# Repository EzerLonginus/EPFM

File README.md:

# EPFM
Building out the projects from Craig Anderton's Book Electronic Projects for Musicians.  

<p>This book was a primary inspiration for me when I was growing up, and I've always wanted to actually complete a good amount of these projects.  The parts listed in the projects were always obsolete or difficult to source.  Having a little more experience than when I was a kid, I took to time to revisit some of these projects.  Not sure I'll post all the projects, since some aren't really projects ("PROJECT 19: Using a Volt Ohm-Millameter"), but maybe I'll try post something in the spirit of those projects.</p>

## OBJECTIVES
- Modify existing schematics with parts that are currently in stock and with similar electrical properties<
- Try to design the PCBs for through hole components to make it easier for more people to create the boards
- Design the PCBs to be friendly with desktop PCB milling machines should one choose to go that route.
    - I tried to keep most of the traces on the bottom side of the board
    - Where top side traces where necessary I kept those straight with large vias so people could just use a jumper wire
- Design the boards and face plate to fit within the Eurorack standard
- Document additional modifications and findings

## PROJECTS (so far)
- PREAMP
- METRONOME
- PASSIVE TONE CONTROL
- HEADPHONE AMP
- MINI AMP
- ULTRA FUZZ

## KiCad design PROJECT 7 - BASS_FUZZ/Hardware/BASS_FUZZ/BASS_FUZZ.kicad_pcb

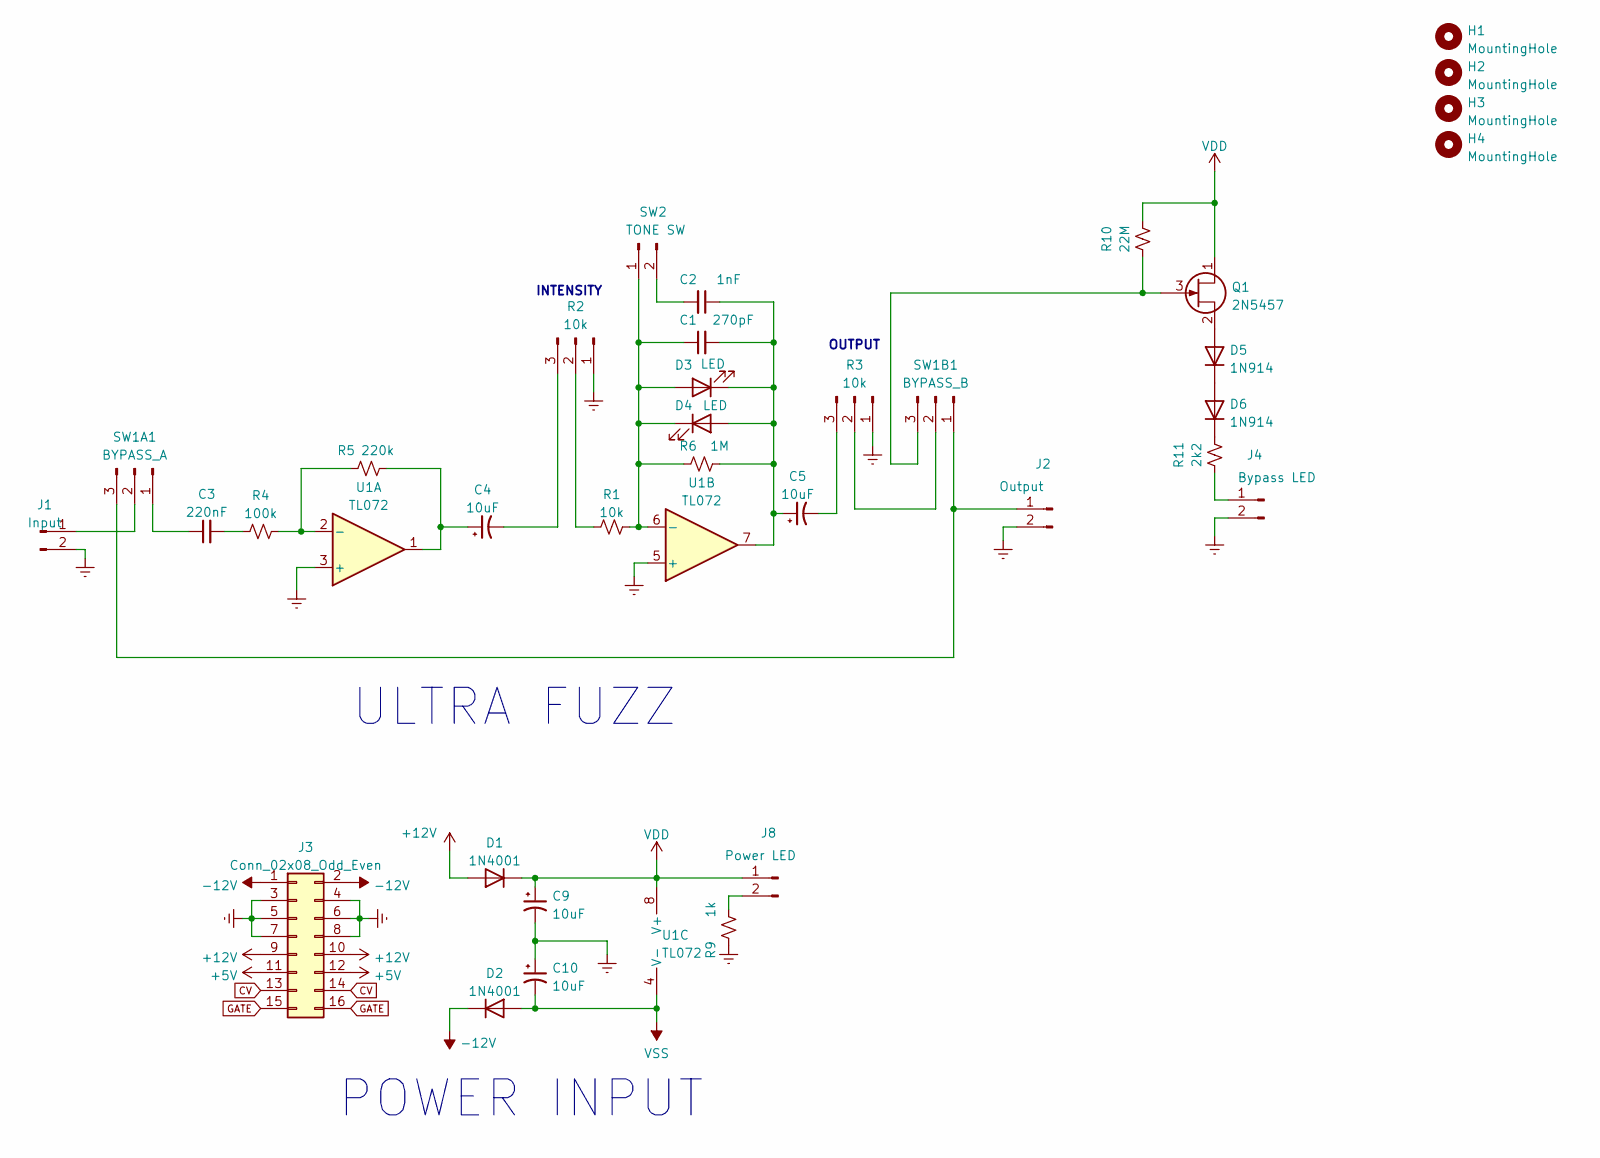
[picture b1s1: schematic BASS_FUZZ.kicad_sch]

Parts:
C1: 270pF; C_Disc_D5.0mm_W2.5mm_P5.00mm
C2: 1nF; C_Disc_D5.0mm_W2.5mm_P5.00mm
C3: 220nF; C_Disc_D5.0mm_W2.5mm_P5.00mm
C4, C5: 10uF; CP_Radial_D8.0mm_P3.80mm
C9, C10: 10uF; CP_Radial_D10.0mm_P3.80mm
D1, D2: 1N4001; D_DO-41_SOD81_P10.16mm_Horizontal
D3, D4: LED; LED_D5.0mm
D5, D6: 1N914; D_DO-35_SOD27_P7.62mm_Horizontal
H1, H2, H3, H4: MountingHole; MountingHole_3.2mm_M3_DIN965_Pad
J1: Input; Molex_SL_171971-0002_1x02_P2.54mm_Vertical
J2: Output; Molex_SL_171971-0002_1x02_P2.54mm_Vertical
J3: Conn_02x08_Odd_Even; IDC-Header_2x08_P2.54mm_Vertical
J4: Bypass LED; Molex_SL_171971-0002_1x02_P2.54mm_Vertical
J8: Power LED; Molex_SL_171971-0002_1x02_P2.54mm_Vertical
Q1: 2N5457; TO-92L_Inline_Wide
R1: 10k; R_Axial_DIN0207_L6.3mm_D2.5mm_P7.62mm_Horizontal
R2, R3: 10k; Molex_SL_171971-0003_1x03_P2.54mm_Vertical
R4: 100k; R_Axial_DIN0207_L6.3mm_D2.5mm_P7.62mm_Horizontal
R5: 220k; R_Axial_DIN0207_L6.3mm_D2.5mm_P7.62mm_Horizontal
R6: 1M; R_Axial_DIN0207_L6.3mm_D2.5mm_P7.62mm_Horizontal
R9: 1k; R_Axial_DIN0207_L6.3mm_D2.5mm_P7.62mm_Horizontal
R10: 22M; R_Axial_DIN0207_L6.3mm_D2.5mm_P7.62mm_Horizontal
R11: 2k2; R_Axial_DIN0207_L6.3mm_D2.5mm_P7.62mm_Horizontal
SW1A1: BYPASS_A; Molex_SL_171971-0003_1x03_P2.54mm_Vertical
SW1B1: BYPASS_B; Molex_SL_171971-0003_1x03_P2.54mm_Vertical
SW2: TONE SW; Molex_SL_171971-0002_1x02_P2.54mm_Vertical
U1: TL072; DIP-8_W7.62mm_Socket_LongPads

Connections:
+5V: J3.11, J3.12
+12V: D1.2 (A), J3.9, J3.10
-12V: D2.1 (K), J3.1, J3.2
CV: J3.13, J3.14
Earth: C9.2, C10.1, J1.2, J2.2, J3.3, J3.4, J3.5, J3.6, J3.7, J3.8, J4.2, R2.1, R3.1, R9.1, U1.3 (+), U1.5 (+)
GATE: J3.15, J3.16
unnamed: C3.1, SW1A1.1
unnamed: C3.2, R4.1
unnamed: D5.1 (K), D6.2 (A)
unnamed: D5.2 (A), Q1.2 (S)
unnamed: D6.1 (K), R11.2
unnamed: J1.1, SW1A1.2
unnamed: J2.1, SW1A1.3, SW1B1.1
unnamed: J4.1, R11.1
unnamed: J8.2, R9.2
unnamed: Q1.3 (G), R10.1, SW1B1.3
unnamed: R1.1, R2.2
unnamed: C4.2, R2.3
unnamed: C5.2, R3.3
unnamed: R4.2, R5.1, U1.2 (-)
unnamed: C4.1, R5.2, U1.1
unnamed: C1.2, C2.1, C5.1, D3.1 (K), D4.2 (A), R6.2, U1.7
unnamed: R3.2, SW1B1.2
unnamed: C2.2, SW2.2
unnamed: C1.1, D3.2 (A), D4.1 (K), R1.2, R6.1, SW2.1, U1.6 (-)
VDD: C9.1, D1.1 (K), J8.1, Q1.1 (D), R10.2, U1.8 (V+)
VSS: C10.2, D2.2 (A), U1.4 (V-)

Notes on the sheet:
POWER INPUT
OUTPUT
INTENSITY
ULTRA FUZZ

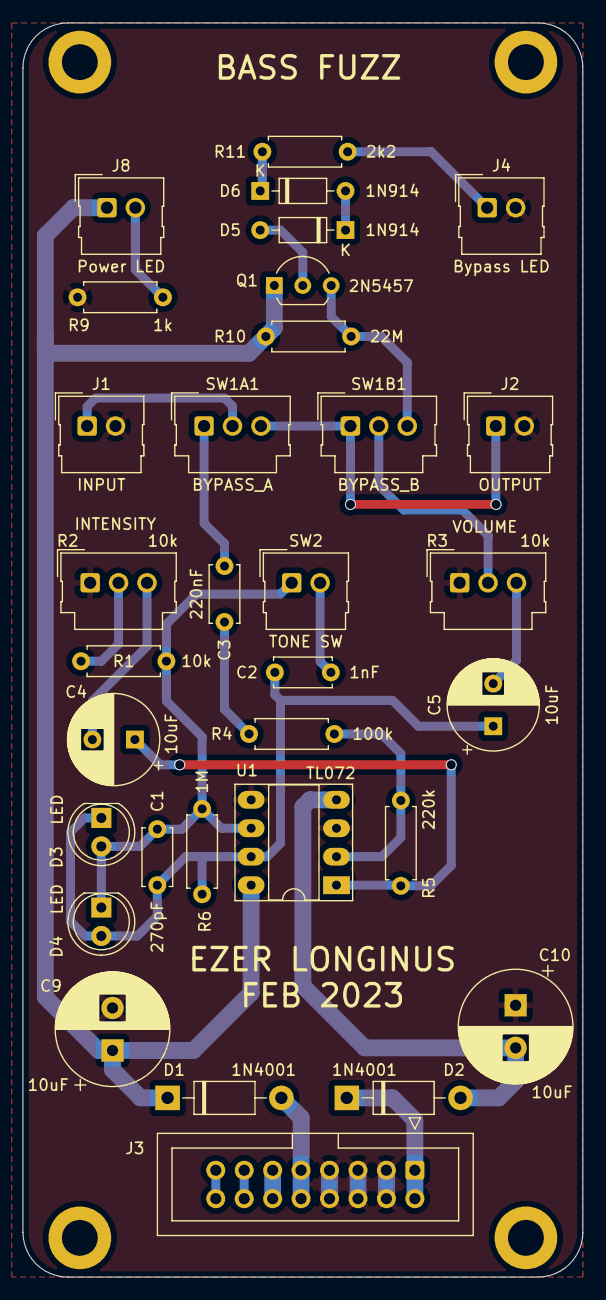
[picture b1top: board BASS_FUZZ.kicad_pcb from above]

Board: 2 copper layers, 50.0 x 112.0 mm, 36 parts (0 on the bottom side), 27 nets.

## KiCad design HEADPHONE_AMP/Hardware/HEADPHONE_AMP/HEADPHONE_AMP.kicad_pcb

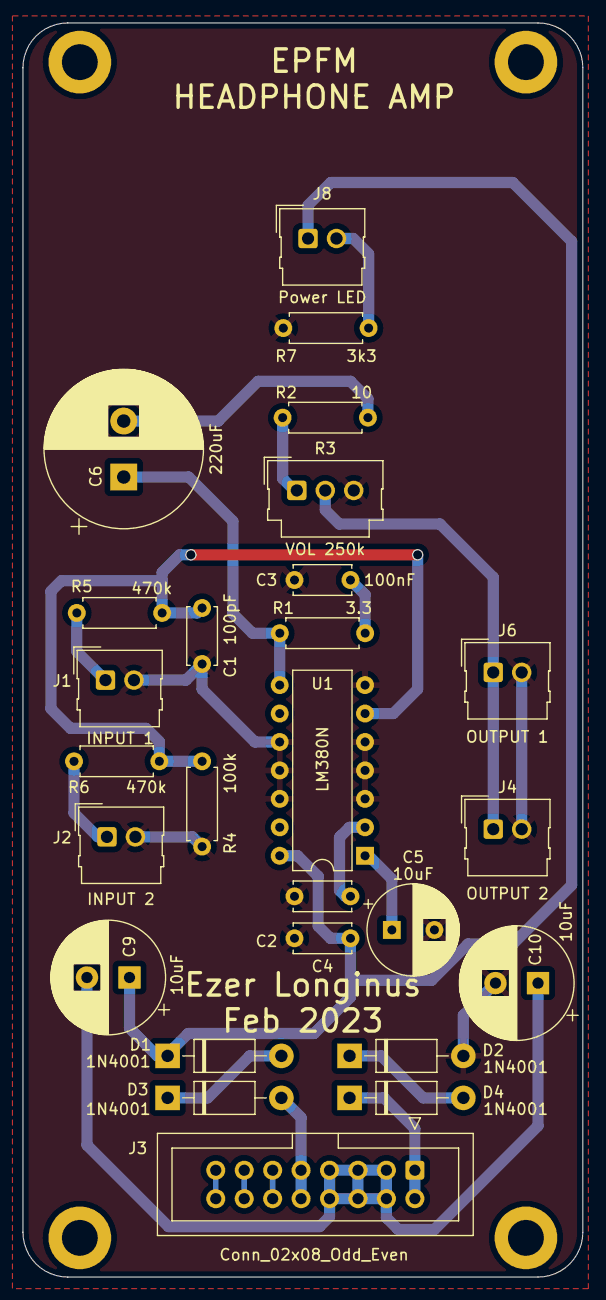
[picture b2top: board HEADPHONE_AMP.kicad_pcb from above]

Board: 2 copper layers, 50.0 x 112.0 mm, 30 parts (0 on the bottom side), 21 nets.

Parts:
C1: 100pF; C_Disc_D5.0mm_W2.5mm_P5.00mm
C2: 10nF; C_Disc_D5.0mm_W2.5mm_P5.00mm
C3, C4: 100nF; C_Disc_D5.0mm_W2.5mm_P5.00mm
C5: 10uF; CP_Radial_D8.0mm_P3.80mm
C6: 220uF; CP_Radial_D14.0mm_P5.00mm
C9, C10: 10uF; CP_Radial_D10.0mm_P3.80mm
D1, D2, D3, D4: 1N4001; D_DO-41_SOD81_P10.16mm_Horizontal
H1, H2, H3, H4: MountingHole; MountingHole_3.2mm_M3_DIN965_Pad
J1: INPUT 1; Molex_SL_171971-0002_1x02_P2.54mm_Vertical
J2: INPUT 2; Molex_SL_171971-0002_1x02_P2.54mm_Vertical
J3: Conn_02x08_Odd_Even; IDC-Header_2x08_P2.54mm_Vertical
J4: OUTPUT 2; Molex_SL_171971-0002_1x02_P2.54mm_Vertical
J6: OUTPUT 1; Molex_SL_171971-0002_1x02_P2.54mm_Vertical
J8: Power LED; Molex_SL_171971-0002_1x02_P2.54mm_Vertical
R1: 3.3; R_Axial_DIN0207_L6.3mm_D2.5mm_P7.62mm_Horizontal
R2: 10; R_Axial_DIN0207_L6.3mm_D2.5mm_P7.62mm_Horizontal
R3: VOL 250k; Molex_SL_171971-0003_1x03_P2.54mm_Vertical
R4: 100k; R_Axial_DIN0207_L6.3mm_D2.5mm_P7.62mm_Horizontal
R5, R6: 470k; R_Axial_DIN0207_L6.3mm_D2.5mm_P7.62mm_Horizontal
R7: 3k3; R_Axial_DIN0207_L6.3mm_D2.5mm_P7.62mm_Horizontal
U1: LM380N; DIP-14_W7.62mm

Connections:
+5V: J3.11, J3.12
+12V: D3.2 (A), J3.9, J3.10
+VDC: C4.1, C9.1, D1.1 (K), J8.1, U1.14 (VS)
-12V: D4.1 (K), J3.1, J3.2
CV: J3.13, J3.14
Earth: C1.1, C2.2, C3.1, C4.2, C5.2, C10.2, D2.2 (A), J1.2, J2.2, J4.2, J6.2, R3.3, R4.1, R7.1, U1.3 (GND), U1.4 (GND), U1.5 (GND), U1.7 (GND), U1.10 (GND), U1.11 (GND), U1.12 (GND)
GATE: J3.15, J3.16
unnamed: C2.1, U1.2 (+)
unnamed: C5.1, U1.1 (BYPASS)
unnamed: D1.2 (A), D3.1 (K)
unnamed: D2.1 (K), D4.2 (A)
unnamed: J1.1, R5.1
unnamed: J2.1, R6.1
unnamed: C9.2, C10.1, J3.3, J3.4, J3.5, J3.6, J3.7, J3.8
unnamed: J8.2, R7.2
unnamed: C6.1, R1.1, U1.8
unnamed: C3.2, R1.2
unnamed: C6.2, R2.1
unnamed: R2.2, R3.1
unnamed: J4.1, J6.1, R3.2
unnamed: C1.2, R4.2, R5.2, R6.2, U1.6 (-)

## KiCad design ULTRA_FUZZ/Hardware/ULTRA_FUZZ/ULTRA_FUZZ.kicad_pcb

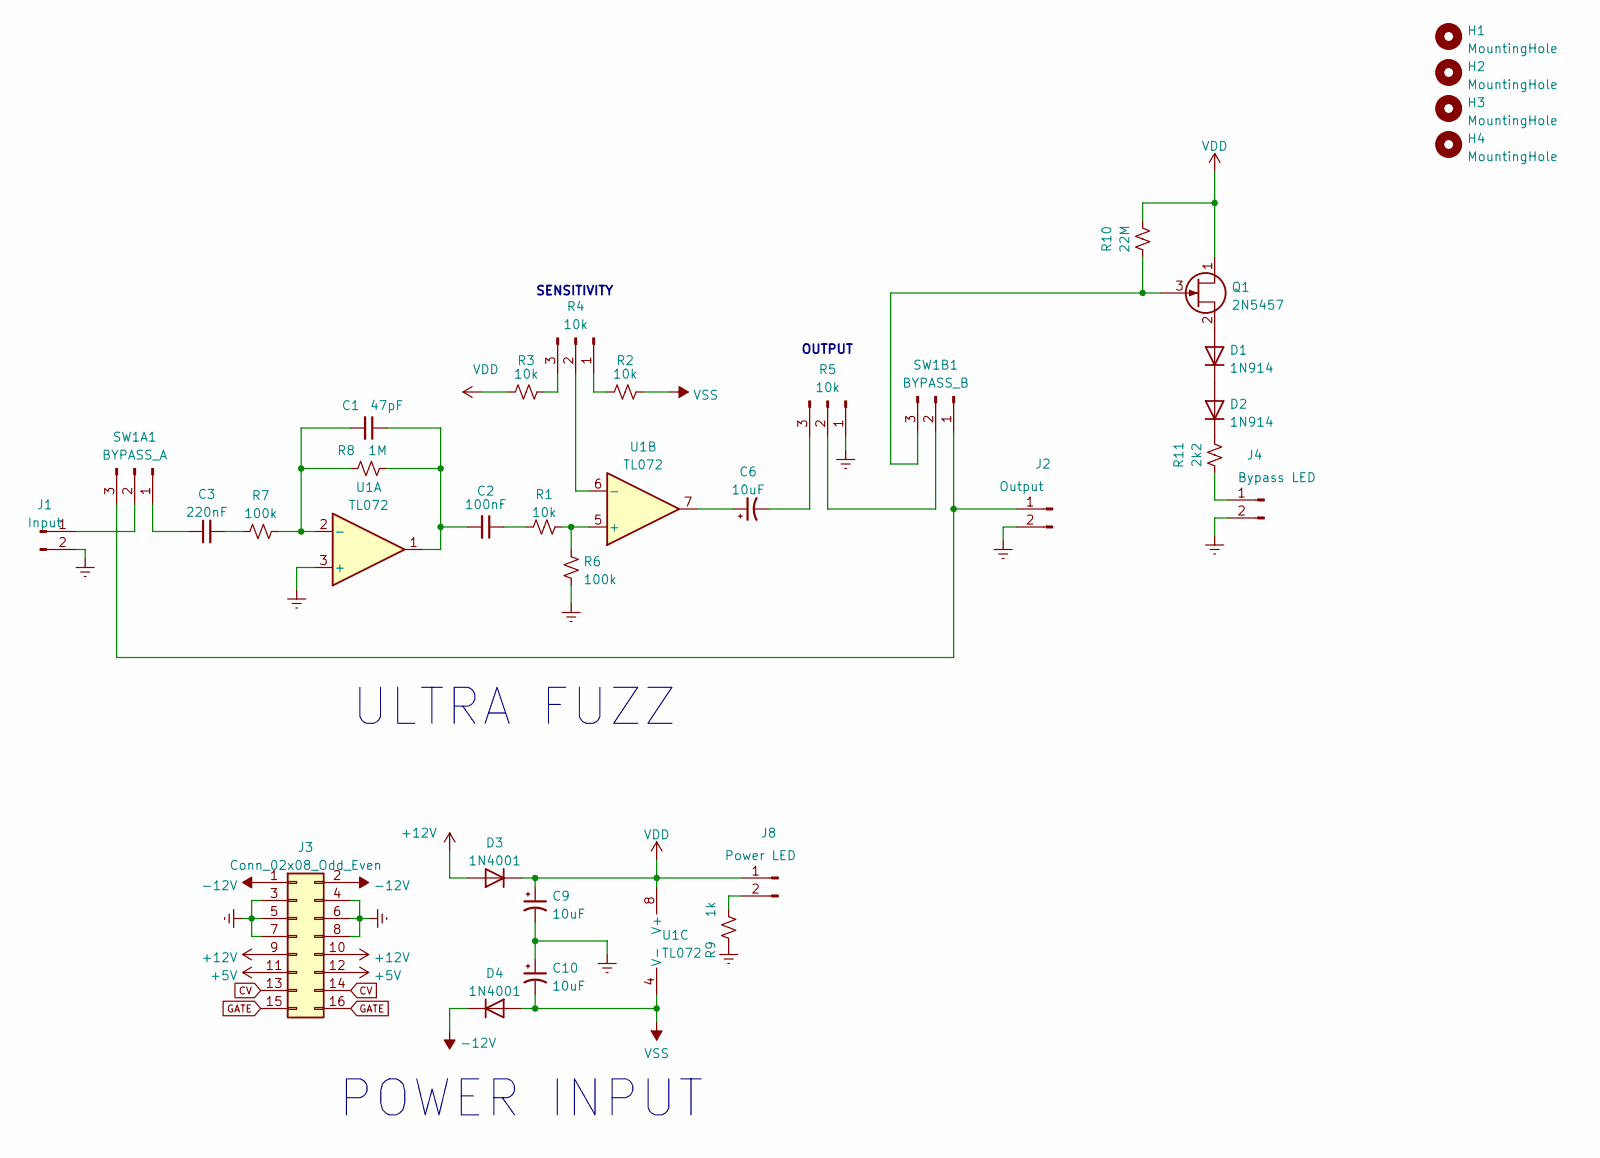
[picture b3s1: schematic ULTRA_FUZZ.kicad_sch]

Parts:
C1: 47pF; C_Disc_D5.0mm_W2.5mm_P5.00mm
C2: 100nF; C_Disc_D5.0mm_W2.5mm_P5.00mm
C3: 220nF; C_Disc_D5.0mm_W2.5mm_P5.00mm
C6: 10uF; CP_Radial_D8.0mm_P3.80mm
C9, C10: 10uF; CP_Radial_D10.0mm_P3.80mm
D1, D2: 1N914; D_DO-35_SOD27_P7.62mm_Horizontal
D3, D4: 1N4001; D_DO-41_SOD81_P10.16mm_Horizontal
H1, H2, H3, H4: MountingHole; MountingHole_3.2mm_M3_DIN965_Pad
J1: Input; Molex_SL_171971-0002_1x02_P2.54mm_Vertical
J2: Output; Molex_SL_171971-0002_1x02_P2.54mm_Vertical
J3: Conn_02x08_Odd_Even; IDC-Header_2x08_P2.54mm_Vertical
J4: Bypass LED; Molex_SL_171971-0002_1x02_P2.54mm_Vertical
J8: Power LED; Molex_SL_171971-0002_1x02_P2.54mm_Vertical
Q1: 2N5457; TO-92L_Inline_Wide
R1, R2, R3: 10k; R_Axial_DIN0207_L6.3mm_D2.5mm_P7.62mm_Horizontal
R4, R5: 10k; Molex_SL_171971-0003_1x03_P2.54mm_Vertical
R6, R7: 100k; R_Axial_DIN0207_L6.3mm_D2.5mm_P7.62mm_Horizontal
R8: 1M; R_Axial_DIN0207_L6.3mm_D2.5mm_P7.62mm_Horizontal
R9: 1k; R_Axial_DIN0207_L6.3mm_D2.5mm_P7.62mm_Horizontal
R10: 22M; R_Axial_DIN0207_L6.3mm_D2.5mm_P7.62mm_Horizontal
R11: 2k2; R_Axial_DIN0207_L6.3mm_D2.5mm_P7.62mm_Horizontal
SW1A1: BYPASS_A; Molex_SL_171971-0003_1x03_P2.54mm_Vertical
SW1B1: BYPASS_B; Molex_SL_171971-0003_1x03_P2.54mm_Vertical
U1: TL072; DIP-8_W7.62mm_Socket_LongPads

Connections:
+5V: J3.11, J3.12
+12V: D3.2 (A), J3.9, J3.10
-12V: D4.1 (K), J3.1, J3.2
CV: J3.13, J3.14
Earth: C9.2, C10.1, J1.2, J2.2, J3.3, J3.4, J3.5, J3.6, J3.7, J3.8, J4.2, R5.1, R6.2, R9.1, U1.3 (+)
GATE: J3.15, J3.16
unnamed: C2.1, R1.1
unnamed: C3.1, SW1A1.1
unnamed: C6.1, U1.7
unnamed: C6.2, R5.3
unnamed: D1.1 (K), D2.2 (A)
unnamed: D1.2 (A), Q1.2 (S)
unnamed: D2.1 (K), R11.2
unnamed: J1.1, SW1A1.2
unnamed: J4.1, R11.1
unnamed: J8.2, R9.2
unnamed: R1.2, R6.1, U1.5 (+)
unnamed: R2.1, R4.1
unnamed: R4.2, U1.6 (-)
unnamed: R3.2, R4.3
unnamed: R5.2, SW1B1.2
unnamed: C3.2, R7.1
unnamed: C1.2, R7.2, R8.1, U1.2 (-)
unnamed: C1.1, C2.2, R8.2, U1.1
unnamed: J2.1, SW1A1.3, SW1B1.1
unnamed: Q1.3 (G), R10.1, SW1B1.3
VDD: C9.1, D3.1 (K), J8.1, Q1.1 (D), R3.1, R10.2, U1.8 (V+)
VSS: C10.2, D4.2 (A), R2.2, U1.4 (V-)

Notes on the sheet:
POWER INPUT
OUTPUT
SENSITIVITY
ULTRA FUZZ

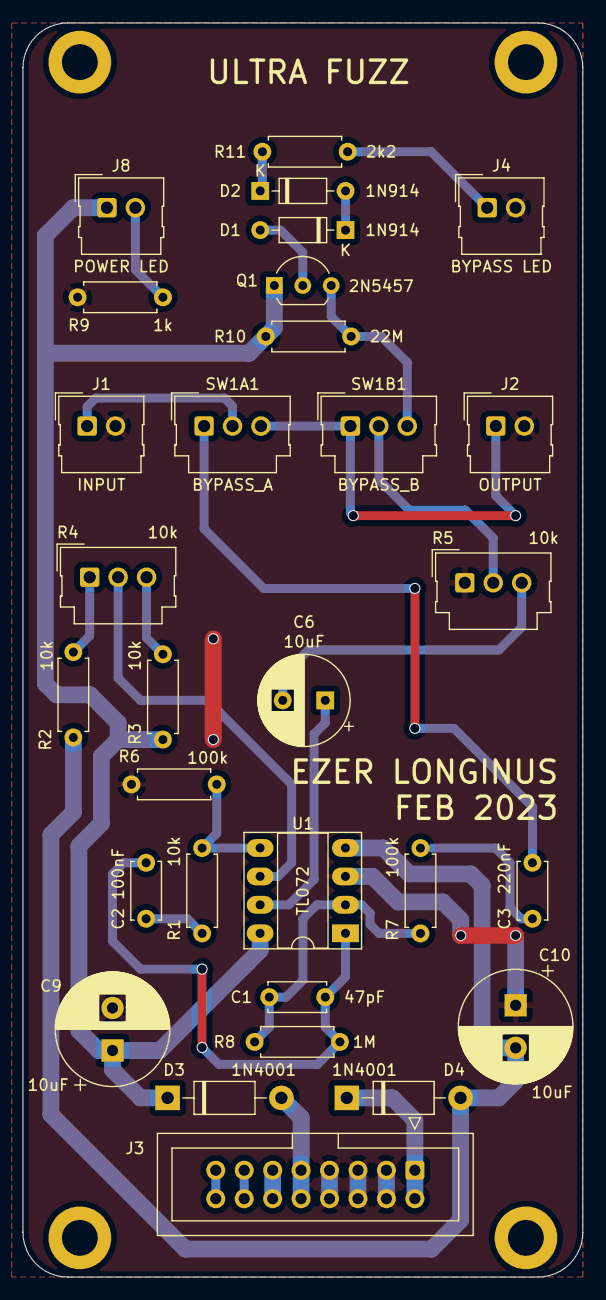
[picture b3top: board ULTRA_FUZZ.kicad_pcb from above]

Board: 2 copper layers, 50.0 x 112.0 mm, 34 parts (0 on the bottom side), 28 nets.

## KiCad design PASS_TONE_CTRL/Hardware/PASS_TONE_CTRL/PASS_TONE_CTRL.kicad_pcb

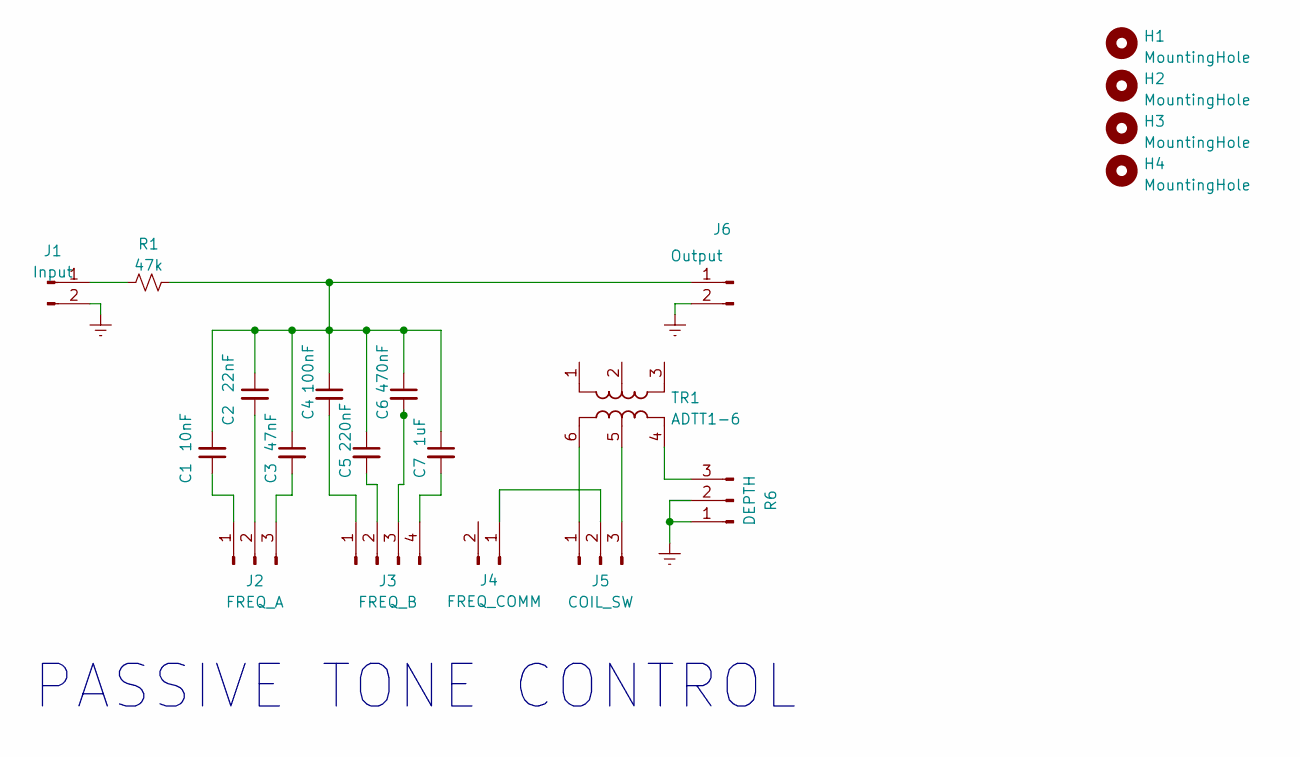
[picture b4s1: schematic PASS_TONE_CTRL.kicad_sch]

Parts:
C1: 10nF; C_Disc_D5.0mm_W2.5mm_P5.00mm
C2: 22nF; C_Disc_D5.0mm_W2.5mm_P5.00mm
C3: 47nF; C_Disc_D5.0mm_W2.5mm_P5.00mm
C4: 100nF; C_Disc_D5.0mm_W2.5mm_P5.00mm
C5: 220nF; C_Disc_D5.0mm_W2.5mm_P5.00mm
C6: 470nF; C_Disc_D5.0mm_W2.5mm_P5.00mm
C7: 1uF; C_Disc_D5.0mm_W2.5mm_P5.00mm
H1, H2, H3, H4: MountingHole; MountingHole_3.2mm_M3_DIN965_Pad
J1: Input; Molex_SL_171971-0002_1x02_P2.54mm_Vertical
J2: FREQ_A; Molex_SL_171971-0003_1x03_P2.54mm_Vertical
J3: FREQ_B; Molex_SL_171971-0004_1x04_P2.54mm_Vertical
J4: FREQ_COMM; Molex_SL_171971-0002_1x02_P2.54mm_Vertical
J5: COIL_SW; Molex_SL_171971-0003_1x03_P2.54mm_Vertical
J6: Output; Molex_SL_171971-0002_1x02_P2.54mm_Vertical
R1: 47k; R_Axial_DIN0207_L6.3mm_D2.5mm_P7.62mm_Horizontal
R6: DEPTH; Molex_SL_171971-0003_1x03_P2.54mm_Vertical
TR1: ADTT1-6; Mini-Circuits_CD637_H5.23mm

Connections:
Earth: J1.2, J6.2, R6.1, R6.2
unnamed: C1.1, J2.1
unnamed: C2.2, J2.2
unnamed: C3.2, J2.3
unnamed: C4.2, J3.1
unnamed: C5.2, J3.2
unnamed: C6.2, J3.3
unnamed: C7.2, J3.4
unnamed: J1.1, R1.1
unnamed: J4.1, J5.2
unnamed: J5.1, TR1.6
unnamed: J5.3, TR1.5
unnamed: C1.2, C2.1, C3.1, C4.1, C5.1, C6.1, C7.1, J6.1, R1.2
unnamed: R6.3, TR1.4

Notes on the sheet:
PASSIVE TONE CONTROL

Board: 2 copper layers, 20 parts (0 on the bottom side), 14 nets, no tracks yet.

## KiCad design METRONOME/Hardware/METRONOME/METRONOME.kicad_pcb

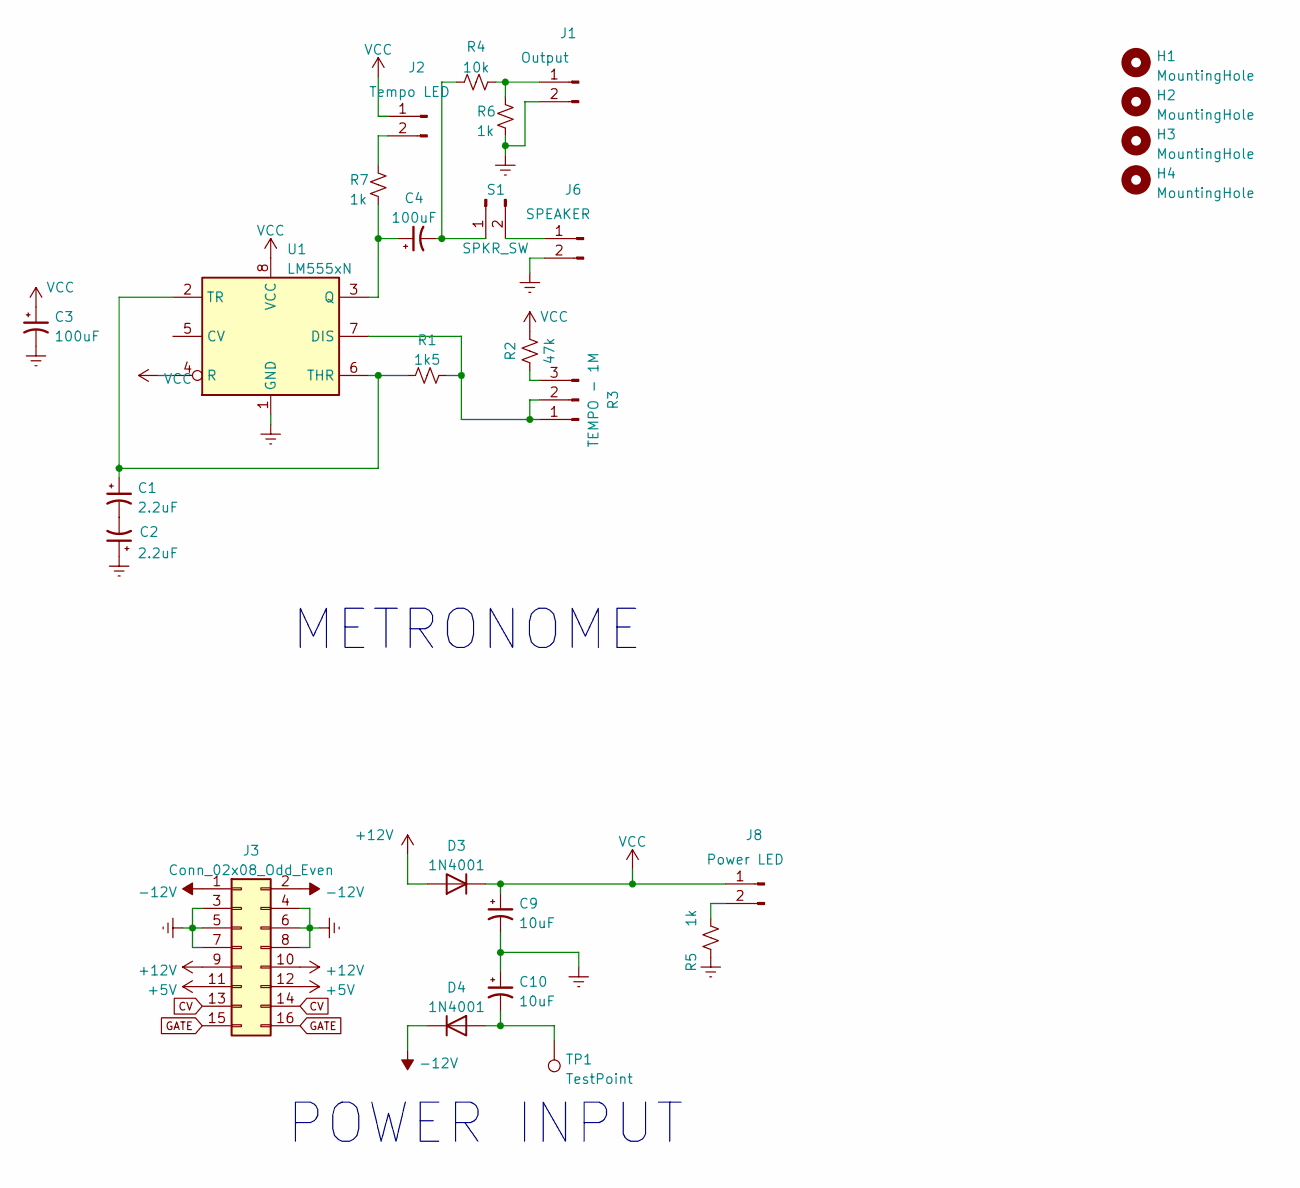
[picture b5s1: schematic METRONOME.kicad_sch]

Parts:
C1, C2: 2.2uF; CP_Radial_D8.0mm_P3.80mm
C3, C4: 100uF; CP_Radial_D10.0mm_P3.80mm
C9, C10: 10uF; CP_Radial_D10.0mm_P3.80mm
D3, D4: 1N4001; D_DO-41_SOD81_P10.16mm_Horizontal
H1, H2, H3, H4: MountingHole; MountingHole_3.2mm_M3_DIN965_Pad
J1: Output; Molex_SL_171971-0002_1x02_P2.54mm_Vertical
J2: Tempo LED; Molex_SL_171971-0002_1x02_P2.54mm_Vertical
J3: Conn_02x08_Odd_Even; IDC-Header_2x08_P2.54mm_Vertical
J6: SPEAKER; Molex_SL_171971-0002_1x02_P2.54mm_Vertical
J8: Power LED; Molex_SL_171971-0002_1x02_P2.54mm_Vertical
R1: 1k5; R_Axial_DIN0207_L6.3mm_D2.5mm_P7.62mm_Horizontal
R2: 47k; R_Axial_DIN0207_L6.3mm_D2.5mm_P7.62mm_Horizontal
R3: TEMPO - 1M; Molex_SL_171971-0003_1x03_P2.54mm_Vertical
R4: 10k; R_Axial_DIN0207_L6.3mm_D2.5mm_P7.62mm_Horizontal
R5, R6, R7: 1k; R_Axial_DIN0207_L6.3mm_D2.5mm_P7.62mm_Horizontal
S1: SPKR_SW; Molex_SL_171971-0002_1x02_P2.54mm_Vertical
TP1: TestPoint; Pin_D1.2mm_L10.2mm_W2.9mm_FlatFork
U1: LM555xN; DIP-8_W7.62mm

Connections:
+5V: J3.11, J3.12
+12V: D3.2 (A), J3.9, J3.10
-12V: D4.1 (K), J3.1, J3.2
CV: J3.13, J3.14
Earth: C2.1, C3.2, C9.2, C10.1, J1.2, J3.3, J3.4, J3.5, J3.6, J3.7, J3.8, J6.2, R5.1, R6.1, U1.1 (GND)
GATE: J3.15, J3.16
unnamed: C1.1, R1.1, U1.2 (TR), U1.6 (THR)
unnamed: C1.2, C2.2
unnamed: C4.1, R7.1, U1.3 (Q)
unnamed: C4.2, R4.1, S1.1
unnamed 10: C10.2, D4.2 (A), TP1.1; also elsewhere on the board
unnamed: J1.1, R4.2, R6.2
unnamed: J2.2, R7.2
unnamed: J6.1, S1.2
unnamed: J8.2, R5.2
unnamed: R1.2, R3.1, R3.2, U1.7 (DIS)
unnamed: R2.2, R3.3
VCC: C3.1, C9.1, D3.1 (K), J2.1, J8.1, R2.1, U1.4 (R), U1.8 (VCC)

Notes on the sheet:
POWER INPUT
METRONOME

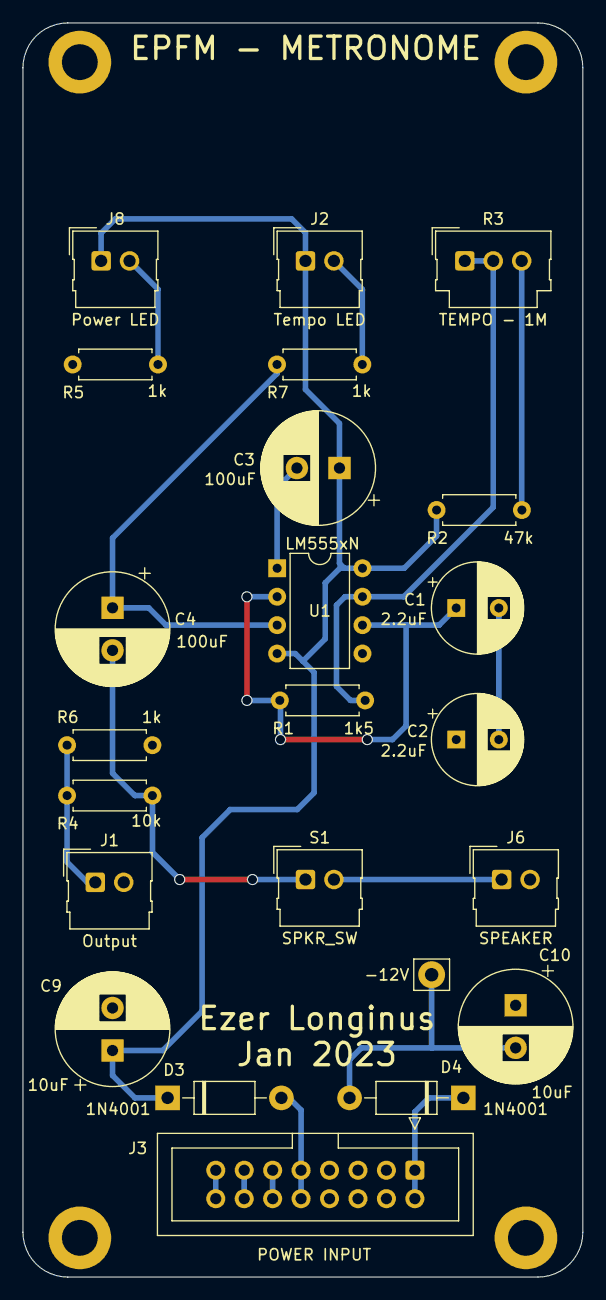
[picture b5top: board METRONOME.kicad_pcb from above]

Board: 2 copper layers, 50.0 x 112.0 mm, 27 parts (0 on the bottom side), 18 nets.

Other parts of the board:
-12V: TestPoint; Pin_D1.2mm_L10.2mm_W2.9mm_FlatFork

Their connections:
unnamed 10: -12V.1; also elsewhere on the board

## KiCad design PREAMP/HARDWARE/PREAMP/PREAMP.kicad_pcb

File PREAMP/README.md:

# PREAMP
This is the first project out of the Electronic Projects for Musicians

## Adjustments and Modifications
<ol>
<li>Swapped the 4739 quad operational amplifier for a more available chip (TL074)</li>
<li>Power Input is based on the Eurorack Standard.  +/-12V, +5V IDC connection</li>
<li>Added a jumper for the VU meter input to either directly connect the balanced output to the meter, or to monitor something else</li>
<li>In order to get a VU meter to function for me, I added some additional diodes and capacitors on the output of U1B</li>
<li>The 1M potentiometer on the output of U1B allows for tuning of the signal to calibrate the VU Meter<li>
</ol>

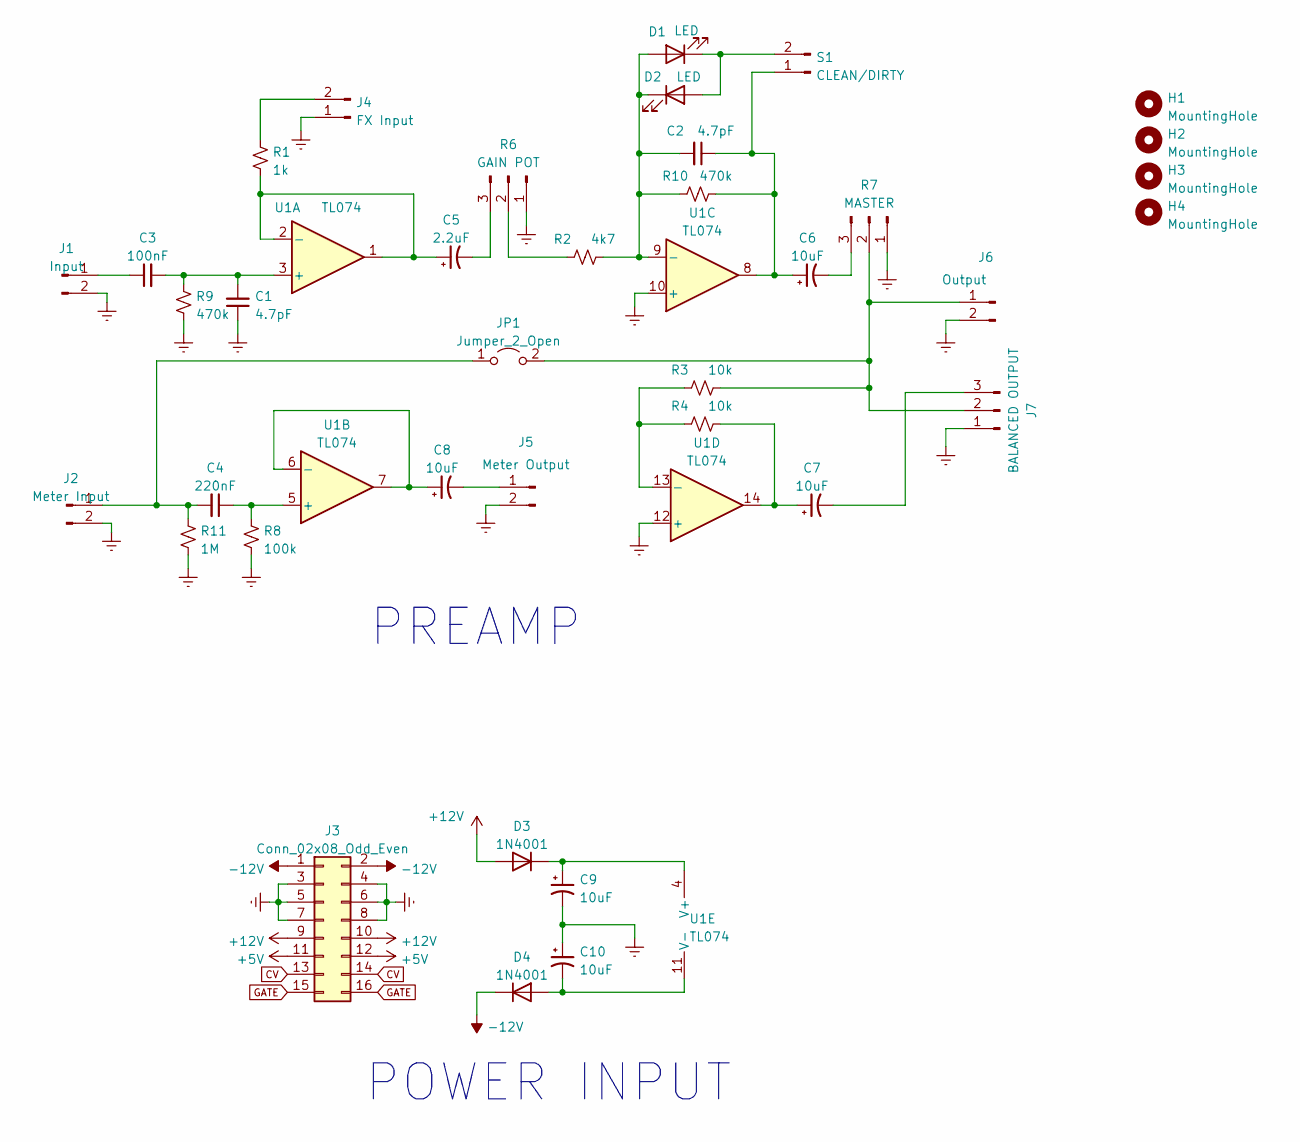
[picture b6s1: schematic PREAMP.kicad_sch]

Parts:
C1, C2: 4.7pF; C_Disc_D5.0mm_W2.5mm_P5.00mm
C3: 100nF; C_Disc_D5.0mm_W2.5mm_P5.00mm
C4: 220nF; C_Disc_D5.0mm_W2.5mm_P5.00mm
C5: 2.2uF; CP_Radial_D8.0mm_P3.80mm
C6, C7, C8: 10uF; CP_Radial_D8.0mm_P3.80mm
C9, C10: 10uF; CP_Radial_D10.0mm_P3.80mm
D1, D2: LED; LED_D5.0mm
D3, D4: 1N4001; D_DO-41_SOD81_P10.16mm_Horizontal
H1, H2, H3, H4: MountingHole; MountingHole_3.2mm_M3_DIN965_Pad
J1: Input; Molex_SL_171971-0002_1x02_P2.54mm_Vertical
J2: Meter Input; Molex_SL_171971-0002_1x02_P2.54mm_Vertical
J3: Conn_02x08_Odd_Even; IDC-Header_2x08_P2.54mm_Vertical
J4: FX Input; Molex_SL_171971-0002_1x02_P2.54mm_Vertical
J5: Meter Output; Molex_SL_171971-0002_1x02_P2.54mm_Vertical
J6: Output; Molex_SL_171971-0002_1x02_P2.54mm_Vertical
J7: BALANCED OUTPUT; Molex_SL_171971-0003_1x03_P2.54mm_Vertical
JP1: Jumper_2_Open; PinSocket_1x02_P2.54mm_Vertical
R1: 1k; R_Axial_DIN0207_L6.3mm_D2.5mm_P7.62mm_Horizontal
R2: 4k7; R_Axial_DIN0207_L6.3mm_D2.5mm_P7.62mm_Horizontal
R3, R4: 10k; R_Axial_DIN0207_L6.3mm_D2.5mm_P7.62mm_Horizontal
R6: GAIN POT; Molex_SL_171971-0003_1x03_P2.54mm_Vertical
R7: MASTER; Molex_SL_171971-0003_1x03_P2.54mm_Vertical
R8: 100k; R_Axial_DIN0207_L6.3mm_D2.5mm_P7.62mm_Horizontal
R9, R10: 470k; R_Axial_DIN0207_L6.3mm_D2.5mm_P7.62mm_Horizontal
R11: 1M; R_Axial_DIN0207_L6.3mm_D2.5mm_P7.62mm_Horizontal
S1: CLEAN/DIRTY; Molex_SL_171971-0002_1x02_P2.54mm_Vertical
U1: TL074; DIP-14_W7.62mm_LongPads

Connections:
+5V: J3.11, J3.12
+12V: D3.2 (A), J3.9, J3.10
-12V: D4.1 (K), J3.1, J3.2
CV: J3.13, J3.14
Earth: C1.1, C9.2, C10.1, J1.2, J2.2, J3.3, J3.4, J3.5, J3.6, J3.7, J3.8, J4.1, J5.2, J6.2, J7.1, R6.1, R7.1, R8.2, R9.2, R11.2, U1.10 (+), U1.12 (+); also elsewhere on the board
GATE: J3.15, J3.16
unnamed: C1.2, C3.2, R9.1, U1.3 (+)
unnamed: C2.1, C6.1, R10.2, S1.1, U1.8
unnamed: C2.2, D1.2 (A), D2.1 (K), R2.2, R10.1, U1.9 (-)
unnamed: C3.1, J1.1
unnamed: C4.1, R8.1, U1.5 (+)
unnamed: C4.2, J2.1, JP1.1 (A), R11.1
unnamed: C5.1, R1.2, U1.1, U1.2 (-)
unnamed: C5.2, R6.3
unnamed: C6.2, R7.3
unnamed: C7.1, R4.2, U1.14
unnamed: C7.2, J7.3
unnamed: C8.1, U1.6 (-), U1.7
unnamed: C8.2, J5.1
unnamed 19: C9.1, D3.1 (K), U1.4 (V+); also elsewhere on the board
unnamed: C10.2, D4.2 (A), U1.11 (V-)
unnamed: D1.1 (K), D2.2 (A), S1.2
unnamed: J4.2, R1.1
unnamed: R2.1, R6.2
unnamed: R3.1, R4.1, U1.13 (-)
unnamed: J6.1, J7.2, JP1.2 (B), R3.2, R7.2

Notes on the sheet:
POWER INPUT
PREAMP

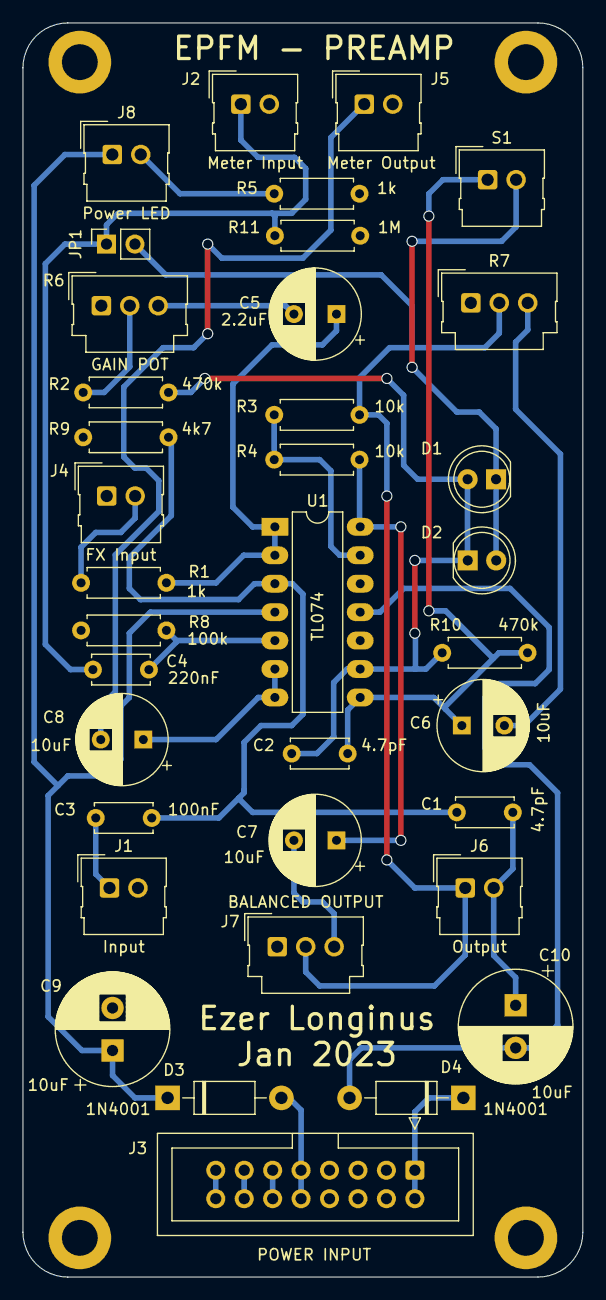
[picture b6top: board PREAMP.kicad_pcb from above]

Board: 2 copper layers, 50.0 x 112.0 mm, 40 parts (0 on the bottom side), 27 nets.

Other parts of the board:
J8: Power LED; Molex_SL_171971-0002_1x02_P2.54mm_Vertical
R5: 1k; R_Axial_DIN0207_L6.3mm_D2.5mm_P7.62mm_Horizontal

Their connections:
Earth: R5.1; also elsewhere on the board
unnamed 19: J8.1; also elsewhere on the board
unnamed: J8.2, R5.2

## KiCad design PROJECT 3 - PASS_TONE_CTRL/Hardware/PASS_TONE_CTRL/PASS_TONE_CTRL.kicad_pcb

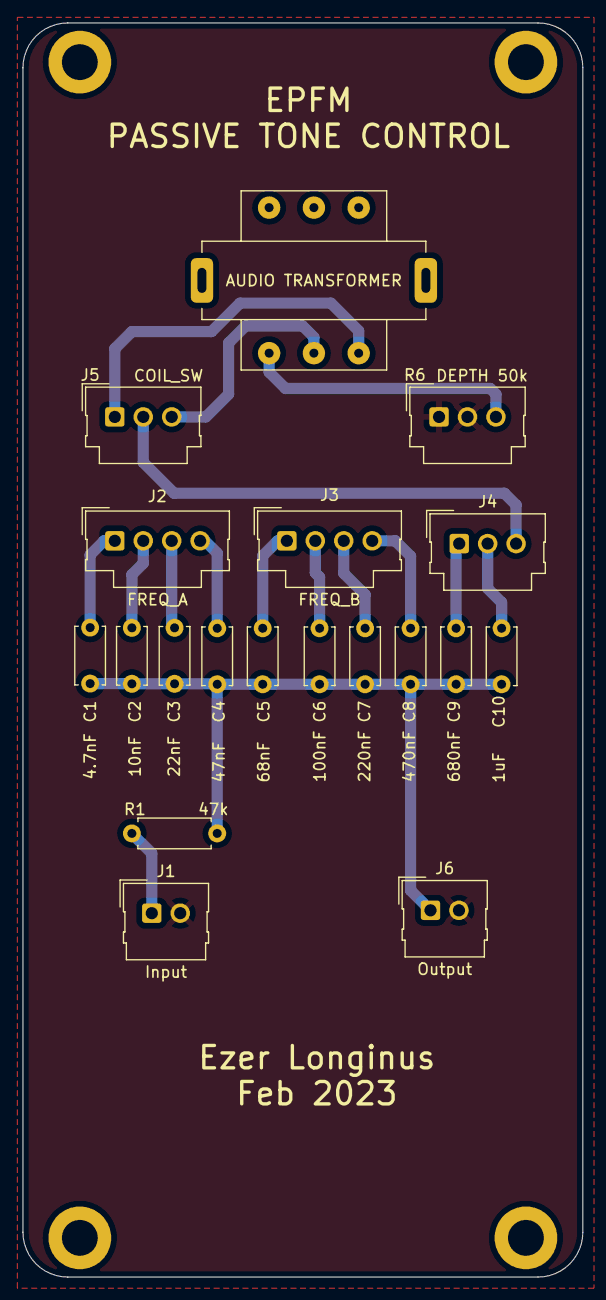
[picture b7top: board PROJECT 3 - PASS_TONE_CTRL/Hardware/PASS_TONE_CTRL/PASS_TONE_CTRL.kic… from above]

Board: 2 copper layers, 50.0 x 112.0 mm, 23 parts (0 on the bottom side), 17 nets.

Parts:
AUDIO TRANSFORMER: ADTT1-6; AudioTransformer_Thru
C1: 4.7nF; C_Disc_D5.0mm_W2.5mm_P5.00mm
C2: 10nF; C_Disc_D5.0mm_W2.5mm_P5.00mm
C3: 22nF; C_Disc_D5.0mm_W2.5mm_P5.00mm
C4: 47nF; C_Disc_D5.0mm_W2.5mm_P5.00mm
C5: 68nF; C_Disc_D5.0mm_W2.5mm_P5.00mm
C6: 100nF; C_Disc_D5.0mm_W2.5mm_P5.00mm
C7: 220nF; C_Disc_D5.0mm_W2.5mm_P5.00mm
C8: 470nF; C_Disc_D5.0mm_W2.5mm_P5.00mm
C9: 680nF; C_Disc_D5.0mm_W2.5mm_P5.00mm
C10: 1uF; C_Disc_D5.0mm_W2.5mm_P5.00mm
H1, H2, H3, H4: MountingHole; MountingHole_3.2mm_M3_DIN965_Pad
J1: Input; Molex_SL_171971-0002_1x02_P2.54mm_Vertical
J2: FREQ_A; Molex_SL_171971-0004_1x04_P2.54mm_Vertical
J3: FREQ_B; Molex_SL_171971-0004_1x04_P2.54mm_Vertical
J4: FREQ_COMM; Molex_SL_171971-0003_1x03_P2.54mm_Vertical
J5: COIL_SW; Molex_SL_171971-0003_1x03_P2.54mm_Vertical
J6: Output; Molex_SL_171971-0002_1x02_P2.54mm_Vertical
R1: 47k; R_Axial_DIN0207_L6.3mm_D2.5mm_P7.62mm_Horizontal
R6: DEPTH 50k; Molex_SL_171971-0003_1x03_P2.54mm_Vertical

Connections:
Earth: J1.2, J6.2, R6.1, R6.2
unnamed: C1.1, J2.1
unnamed: C2.1, J2.2
unnamed: C3.2, J2.3
unnamed: C4.2, J2.4
unnamed: C5.2, J3.1
unnamed: C6.2, J3.2
unnamed: C7.2, J3.3
unnamed: C1.2, C2.2, C3.1, C4.1, C5.1, C6.1, C7.1, C8.1, C9.1, C10.1, J6.1, R1.2
unnamed: C8.2, J3.4
unnamed: C9.2, J4.1
unnamed: C10.2, J4.2
unnamed: J1.1, R1.1
unnamed: AUDIO TRANSFORMER.6, J5.1
unnamed: J4.3, J5.2
unnamed: AUDIO TRANSFORMER.5, J5.3
unnamed: AUDIO TRANSFORMER.4, R6.3
